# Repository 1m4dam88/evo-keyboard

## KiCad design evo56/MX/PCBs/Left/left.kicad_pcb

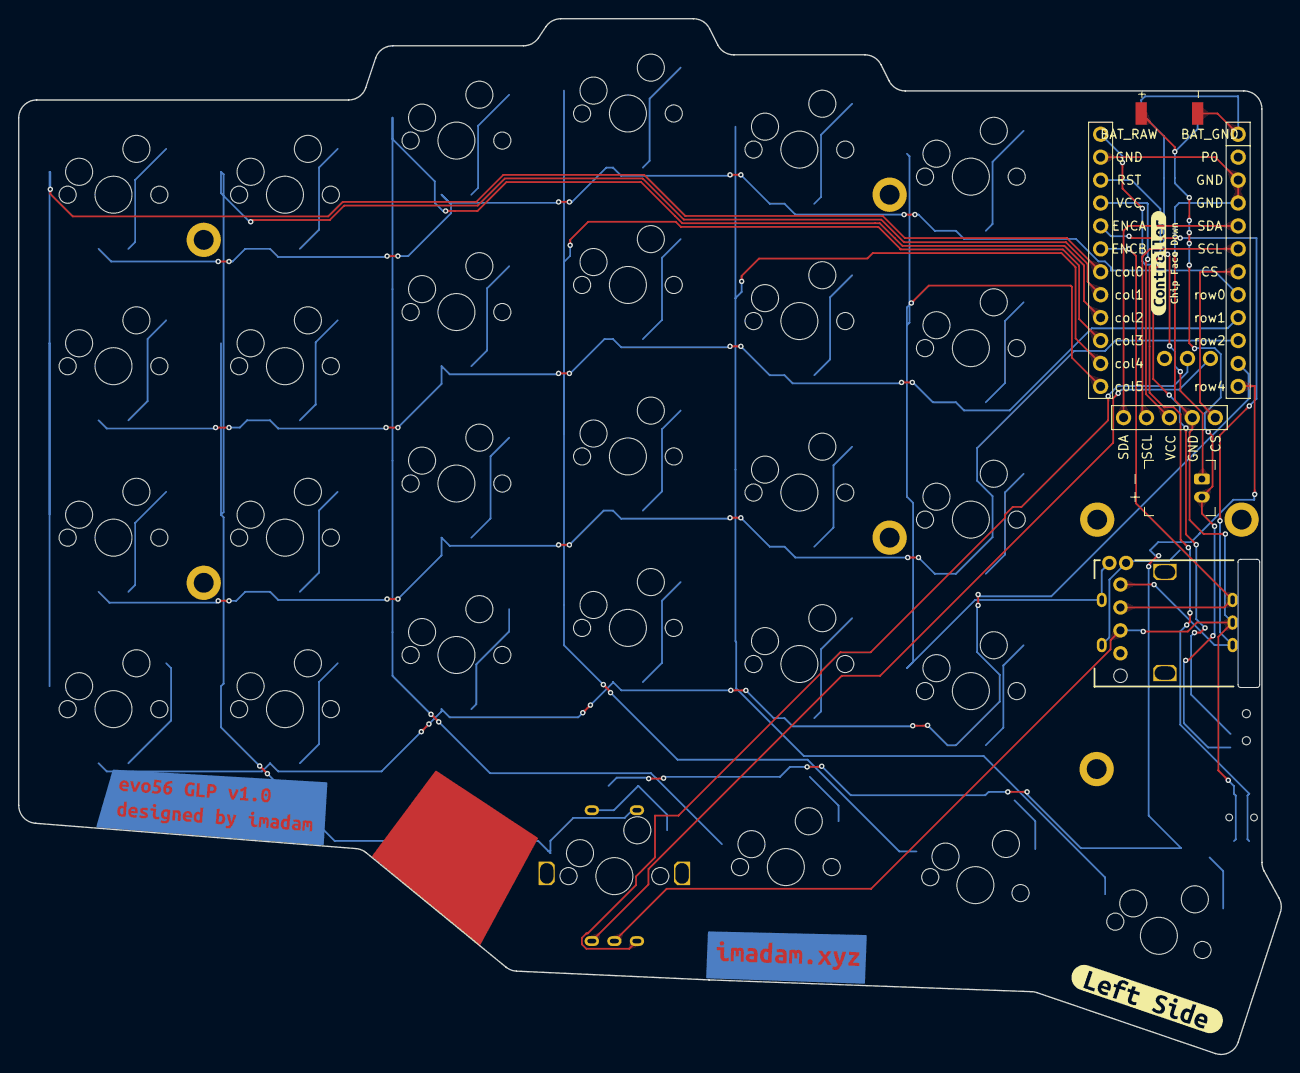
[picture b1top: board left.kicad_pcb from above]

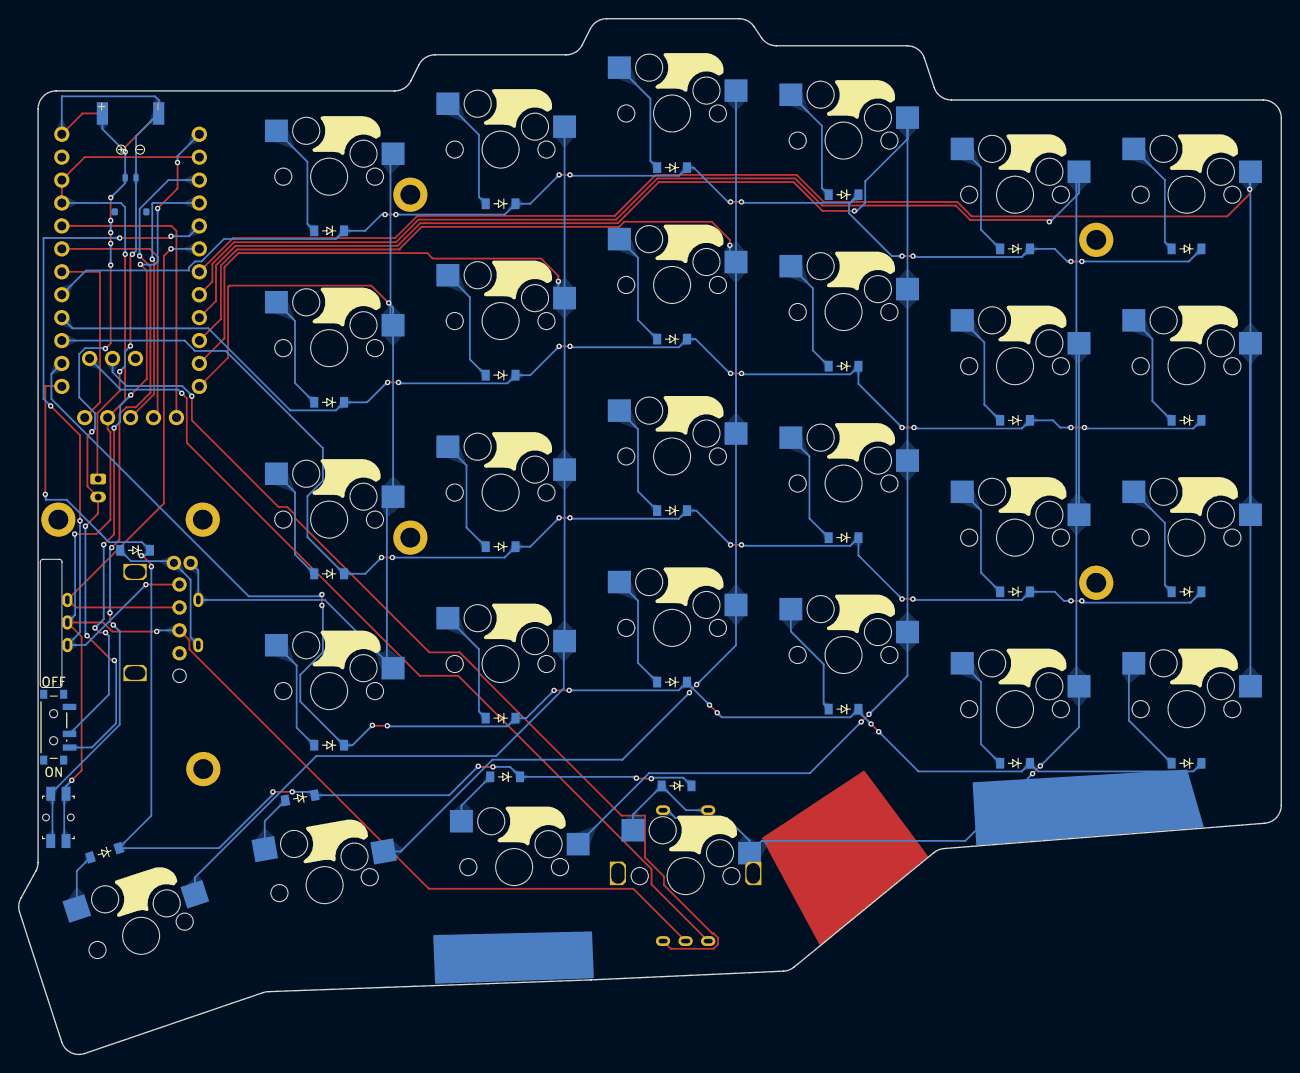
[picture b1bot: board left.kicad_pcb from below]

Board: 2 copper layers, 139.9 x 114.8 mm, 78 parts (62 on the bottom side), 53 nets.

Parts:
Board_0-kibuzzard-67FD9A83: G***; kibuzzard-67FD9A83
Board_0-kibuzzard-67FD52AD: G***; kibuzzard-67FD52AD
Board_0-kibuzzard-67FD5276: G***; kibuzzard-67FD5276
Board_0-kibuzzard-67FD5311: G***; kibuzzard-67FD5311
Board_0-kibuzzard-67FD5341: G***; kibuzzard-67FD5341
CONN1: battery_connector_molex_pico_ezmate_1x02
D1, D2, D3, D4, D5, D6, D7, D8, D9, D10, D11, D12, D13, D14, D15, D16, D17, D18, D19, D20, D21, D22, D23, D24, D25, D26, D27, D28, D29: diode_tht_sod123
DISP1: display_nice_view
H1, H2, H3, H4, H5, H11, H12: mounting_hole_plated
JST1: battery_connector_jst_ph_2
MCU1: mcu_supermini_nrf52840
PAD1: pads
PWR1: power_switch_smd_side
RE1, RE2: rotary_encoder_ec11_ec12
RST1: reset_switch_smd_side
S1, S2, S3, S4, S5, S6, S7, S8, S9, S10, S11, S12, S13, S14, S15, S16, S17, S18, S19, S20, S21, S22, S23, S24, S25, S26, S27, S28: switch_mx

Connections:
BAT_GND: CONN1.2, JST1.1, MCU1.1, PAD1.1, PAD1.2
BAT_RAW: MCU1.24, PWR1.2
CS: DISP1.5, MCU1.7
ENCA: MCU1.20, RE1.A
ENCB: MCU1.19, RE1.C
ENCC: MCU1.25, RE2.A
ENCD: MCU1.26, RE2.C
GND: DISP1.4, MCU1.3, MCU1.4, MCU1.23, RE1.B, RE2.B, RST1.2, RST1.4
ON_P: CONN1.1, JST1.2, PAD1.1, PAD1.2, PWR1.3
RST: MCU1.22, RST1.1, RST1.3
SCL: DISP1.2, MCU1.6
SDA: DISP1.1, MCU1.5
VCC: DISP1.3, MCU1.21
col0: MCU1.18, S1.1, S2.1, S3.1, S4.1
col1: MCU1.17, RE2.S1, S5.1, S6.1, S7.1, S8.1, S25.1
col2: MCU1.16, S9.1, S10.1, S11.1, S12.1, S26.1
col3: MCU1.15, S13.1, S14.1, S15.1, S16.1, S27.1
col4: MCU1.14, S17.1, S18.1, S19.1, S20.1, S28.1
col5: MCU1.13, RE1.S1, S21.1, S22.1, S23.1, S24.1
home_cluster: D26.2, S26.2
index_bottom: D17.2, S17.2
index_home: D18.2, S18.2
index_num: D20.2, S20.2
index_top: D19.2, S19.2
inner_bottom: D21.2, S21.2
inner_cluster: D25.2, RE2.S2, S25.2
inner_home: D22.2, S22.2
inner_num: D24.2, S24.2
inner_top: D23.2, S23.2
layer_cluster: D27.2, S27.2
middle_bottom: D13.2, S13.2
middle_home: D14.2, S14.2
middle_num: D16.2, S16.2
middle_top: D15.2, S15.2
outer_bottom: D1.2, S1.2
outer_home: D2.2, S2.2
outer_num: D4.2, S4.2
outer_top: D3.2, S3.2
pinky_bottom: D5.2, S5.2
pinky_home: D6.2, S6.2
pinky_num: D8.2, S8.2
pinky_top: D7.2, S7.2
ring_bottom: D9.2, S9.2
ring_home: D10.2, S10.2
ring_num: D12.2, S12.2
ring_top: D11.2, S11.2
row0: D4.1, D8.1, D12.1, D16.1, D20.1, D24.1, MCU1.8
row1: D3.1, D7.1, D11.1, D15.1, D19.1, D23.1, MCU1.9
row2: D2.1, D6.1, D10.1, D14.1, D18.1, D22.1, MCU1.10
row3: D1.1, D5.1, D9.1, D13.1, D17.1, D21.1, MCU1.11
row4: D25.1, D26.1, D27.1, D28.1, D29.1, MCU1.12
scrollwheel_enc: D29.2, RE1.S2
space_cluster: D28.2, S28.2

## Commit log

2025-02-24 left pcb initial commit
2025-02-24 left and right mostly finished
2025-02-25 added fill
2025-03-19 layout
2025-03-20 change outline
2025-03-20 remove old PCBs
2025-04-05 almost finsihed ergogen config for glp
2025-04-05 pcb finalized i think
2025-04-06 update outlines
2025-04-07 er i lied
2025-04-07 modularise more
2025-04-08 redo outine
2025-04-09 40% > 50%
2025-04-09 make 2 layouts, 44 and 56.
2025-04-18 finish right glp pcb
